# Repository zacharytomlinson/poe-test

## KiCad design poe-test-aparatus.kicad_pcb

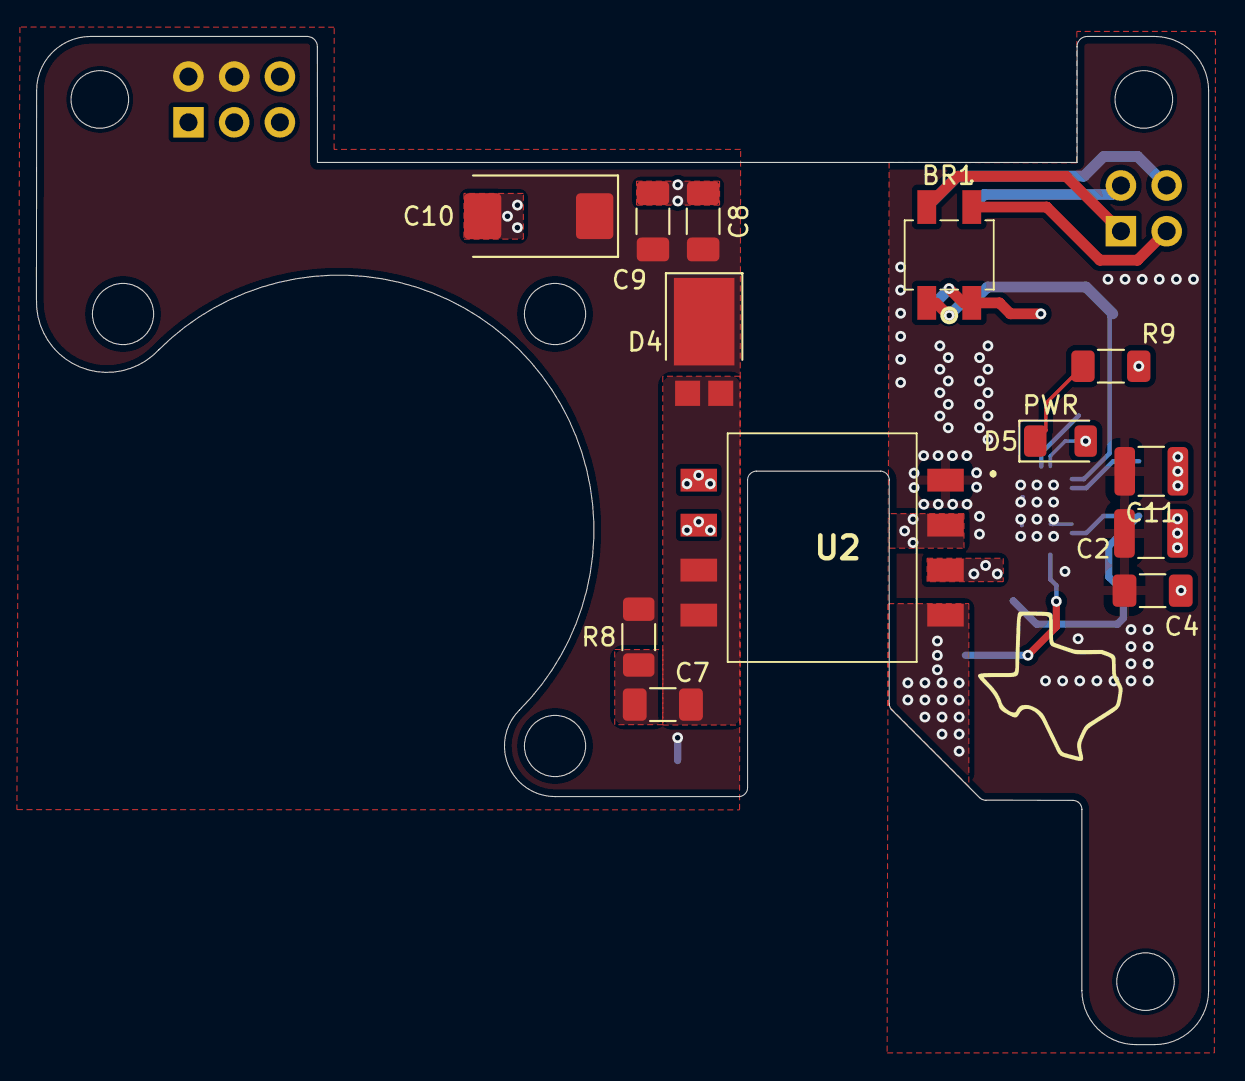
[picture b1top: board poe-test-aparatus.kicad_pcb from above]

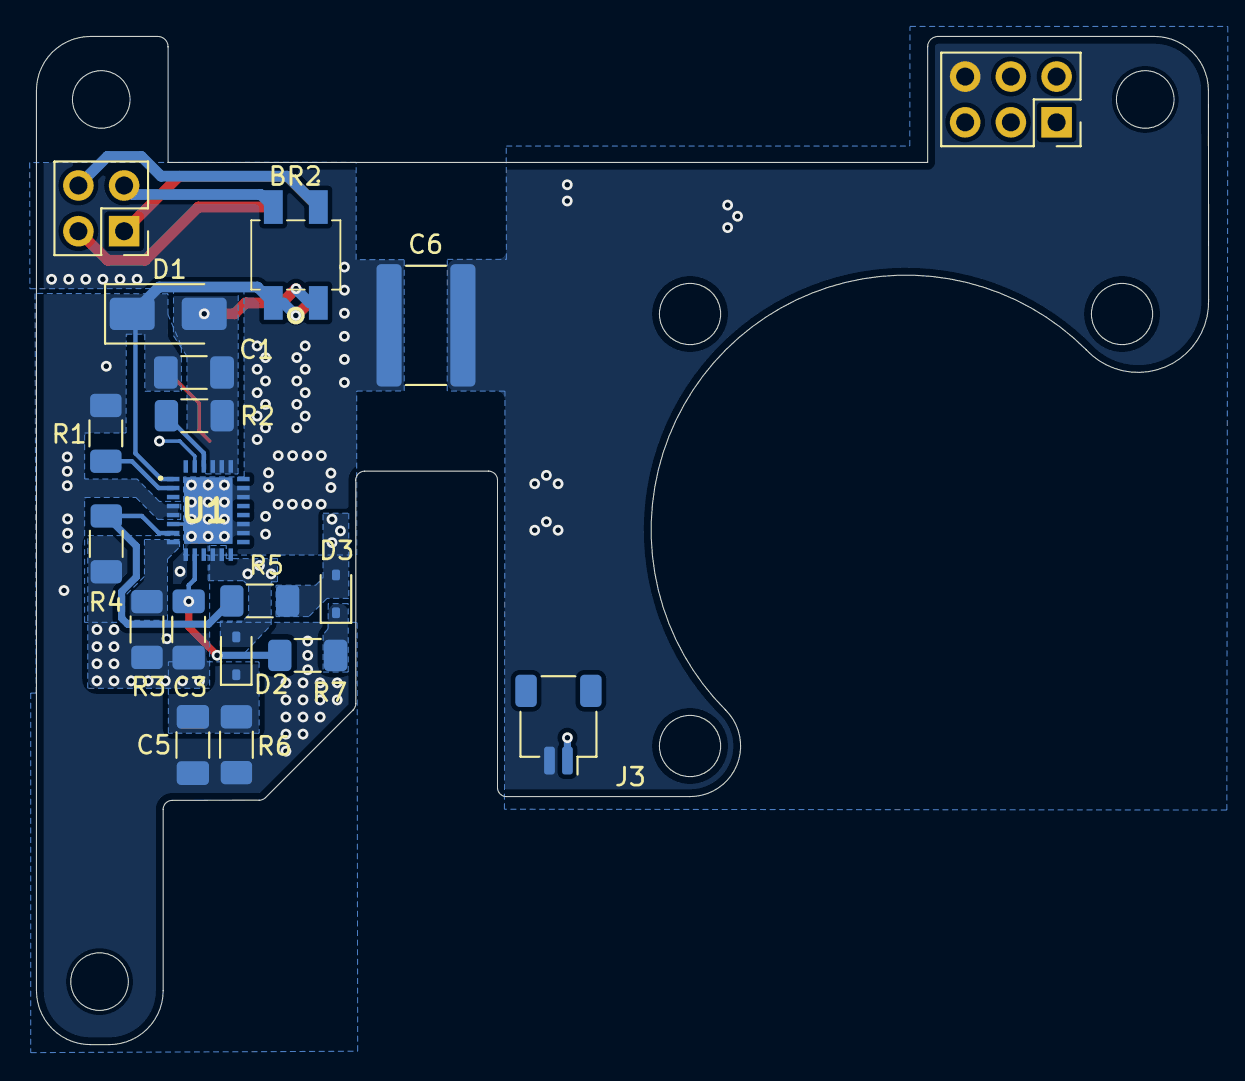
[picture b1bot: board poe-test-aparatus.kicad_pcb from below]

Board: 2 copper layers, 65.1 x 56.0 mm, 35 parts (19 on the bottom side), 22 nets.

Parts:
BR1, BR2: MB10F-13; MB10F13
C1: 0.1uF; C_1206_3216Metric_Pad1.33x1.80mm_HandSolder
C2, C11: 10uF; C_1210_3225Metric
C3: 1uF; C_1206_3216Metric_Pad1.33x1.80mm_HandSolder
C4: 2u2; C_1206_3216Metric_Pad1.33x1.80mm_HandSolder
C5: 10nF; C_1206_3216Metric_Pad1.33x1.80mm_HandSolder
C6: 2.2nF; C_1825_4564Metric
C7: 1nF; C_1206_3216Metric_Pad1.33x1.80mm_HandSolder
C8, C9: 47uF; C_1206_3216Metric_Pad1.33x1.80mm_HandSolder
C10: 470uF; CP_EIA-7343-43_Kemet-X
D1: SMAJ58A; D_SMA
D2: BAV21; D_SOD-323
D3: 1N4148; D_SOD-323
D4: SBR8U60P5-7; D_PowerDI-5
D5: PWR; LED_1206_3216Metric
H1, H2, H3: MountingHole; MountingHole_3.2mm_M3_ISO14580
J1: Power Injector; PinSocket_2x03_P2.54mm_Vertical
J2: PoE Header; PinSocket_2x02_P2.54mm_Vertical
J3: Conn_01x02_Pin; JST_SH_SM02B-SRSS-TB_1x02-1MP_P1.00mm_Horizontal
R1: 24.9k; R_1206_3216Metric_Pad1.30x1.75mm_HandSolder
R2: 41.2R; R_1206_3216Metric_Pad1.30x1.75mm_HandSolder
R3: 49.9k; R_1206_3216Metric_Pad1.30x1.75mm_HandSolder
R4: 17.8k; R_1206_3216Metric_Pad1.30x1.75mm_HandSolder
R5: 110k; R_1206_3216Metric_Pad1.30x1.75mm_HandSolder
R6: 10k; R_1206_3216Metric_Pad1.30x1.75mm_HandSolder
R7, R9: 1k; R_1206_3216Metric_Pad1.30x1.75mm_HandSolder
R8: 20R; R_1206_3216Metric_Pad1.30x1.75mm_HandSolder
U1: MP8007; MP8007GVZ
U2: POE70P-50L; POE70P50LD

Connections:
/+: BR1.1 (+), J2.3
/+5V@1.4A: C8.1, C9.1, C10.1, D4.1 (K), J1.2, J1.4, J3.1, R8.1
/TR0_TAP: BR1.3 (_), J2.1
/TR2_TAP: BR2.3 (_), J2.2
/TR3_TAP: BR2.1 (+), J2.4
GND: C6.1, C8.2, C9.2, C10.2, J1.6, J3.2, U2.7 (S2-), U2.8 (S-)
GNDPWR: C2.2, C3.2, C4.2, C6.2, C11.2, R3.2, R4.2, U1.6 (MODE), U1.9 (AGND), U1.16 (GND), U1.17, U1.20 (RTN), U1.21, U1.29 (GND), U2.1 (B-)
unnamed: BR1.2 (~_1), BR2.2 (~_1), C1.2, D1.2 (A2), R2.1, U1.23 (VSS), U1.24, U1.25 (FTY)
unnamed: BR1.4 (~_2), BR2.4 (~_2), C1.1, C2.1, C4.1, C5.1, C11.1, D1.1 (A1), R1.1, R6.1, R9.1, U1.1 (AUX), U1.4 (VDD), U1.5 (FB2), U2.4 (P-)
unnamed: C7.1, R8.2
unnamed: D2.2 (A), U1.12 (SW), U1.13, U2.3 (P+)
unnamed: C5.2, D2.1 (K), R6.2
unnamed: D3.2 (A), R5.1, U2.2 (B+)
unnamed: D3.1 (K), R7.1
unnamed: C7.2, D4.2 (A), U2.5 (S2+), U2.6 (S+)
unnamed: D5.1 (A), R9.2
unnamed: D5.2 (K), U1.27 (T2P)
unnamed: R2.2, U1.26 (CLASS)
unnamed: R1.2, U1.2 (DET)
unnamed: R4.1, R5.2, U1.7 (FB1)
unnamed: R3.1, U1.8 (ILIM)
unnamed: C3.1, R7.2, U1.10 (VCC)

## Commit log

2024-05-23 ignoring backups
2024-05-23 ignoring autosaves
2024-05-23 remove mas
2024-05-23 more removal
2024-09-03 Rework with better layout and resistors fix tests
2024-09-03 Remove unnecessary
2024-10-16 moderate updates
2024-10-16 cleanup
2024-10-16 Final clean up for now
2024-10-16 testing new gitignore
2024-10-16 clean AGAIN
2024-10-16 Fixed flipped rectifier diode input
2024-10-16 adjust resistor value
